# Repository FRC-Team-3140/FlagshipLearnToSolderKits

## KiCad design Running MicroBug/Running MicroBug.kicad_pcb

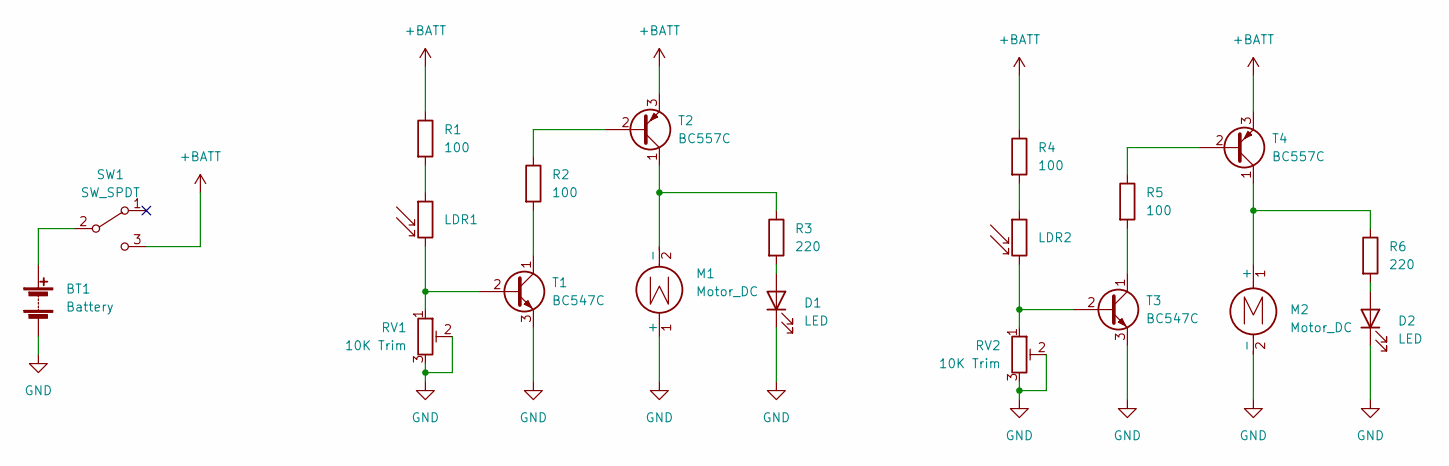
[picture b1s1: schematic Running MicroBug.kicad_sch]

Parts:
BT1: Battery; BatteryHolder_Keystone_2468_2xAAA
D1, D2: LED; LED_D3.0mm
LDR1, LDR2: LDR07; R_LDR_5.1x4.3mm_P3.4mm_Vertical
M1, M2: Motor_DC; 18mm square hobby motor
R1, R2, R4, R5: 100; R_Axial_DIN0207_L6.3mm_D2.5mm_P10.16mm_Horizontal
R3, R6: 220; R_Axial_DIN0207_L6.3mm_D2.5mm_P10.16mm_Horizontal
RV1, RV2: 10K Trim; Potentiometer_Vertical
SW1: SW_SPDT; Switch_SPDT_Straight
T1, T3: BC547C; TO-92_Inline
T2, T4: BC557C; TO-92_Inline

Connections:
+BATT: R1.1, R4.1, SW1.3 (C), T2.3 (E), T4.3 (E)
GND: BT1.2 (-), D1.1 (K), D2.1 (K), M1.1 (+), M2.2 (-), RV1.2, RV1.3, RV2.2, RV2.3, T1.3 (E), T3.3 (E)
unnamed: BT1.1 (+), SW1.2 (B)
unnamed: D1.2 (A), R3.2
unnamed: D2.2 (A), R6.2
unnamed: LDR1.1, R1.2
unnamed: LDR1.2, RV1.1, T1.2 (B)
unnamed: LDR2.1, R4.2
unnamed: LDR2.2, RV2.1, T3.2 (B)
unnamed: R2.1, T2.2 (B)
unnamed: R2.2, T1.1 (C)
unnamed: M1.2 (-), R3.1, T2.1 (C)
unnamed: R5.1, T4.2 (B)
unnamed: R5.2, T3.1 (C)
unnamed: M2.1 (+), R6.1, T4.1 (C)

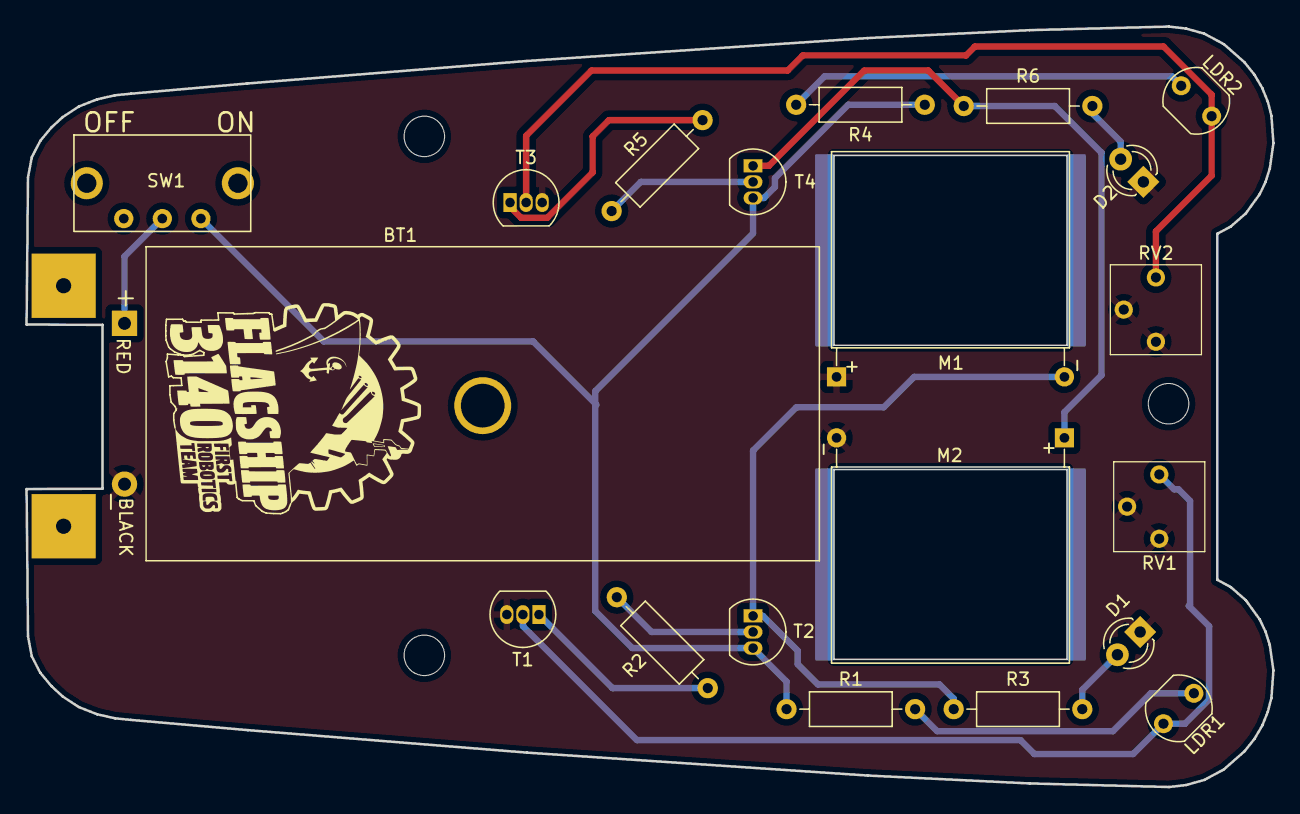
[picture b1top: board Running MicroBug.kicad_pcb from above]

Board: 2 copper layers, 98.5 x 60.1 mm, 20 parts (0 on the bottom side), 15 nets.

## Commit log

2023-04-05 add .gitignore
2023-04-05 add files in 2022 state
2023-06-21 add ibom
